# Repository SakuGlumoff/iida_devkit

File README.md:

# Iida devkit

PCB design exercise

## Hardware

Hardware design related files can be found in the `hardware` directory.
To get started with hardware development, take a look at the _README_ file therein.

The harware was designed with [KiCad EDA](https://www.kicad.org/) and manufactured with [Aisler](https://aisler.net/).

## Firmware

Firmware source files can be found in the `firmware` directory.
To get started with firmware development, take a look at the _README_ file therein.

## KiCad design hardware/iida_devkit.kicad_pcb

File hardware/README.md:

# Hardware

Hardware for Iida devkit.

## Requirements

| Tool  | Version |
|-------|---------|
| KiCad | >= 8    |
| Git   | >= 2.34 |

## How to get started

Install the required version of _KiCad_ from https://www.kicad.org/download/.
Install the required version of _Git_ from https://git-scm.com/downloads.
Download the symbol and part libraries used in this project by running `git submodule update --init --recursive`.
You can now open the project file `iida_devkit.kicad_pro` with _KiCad_.

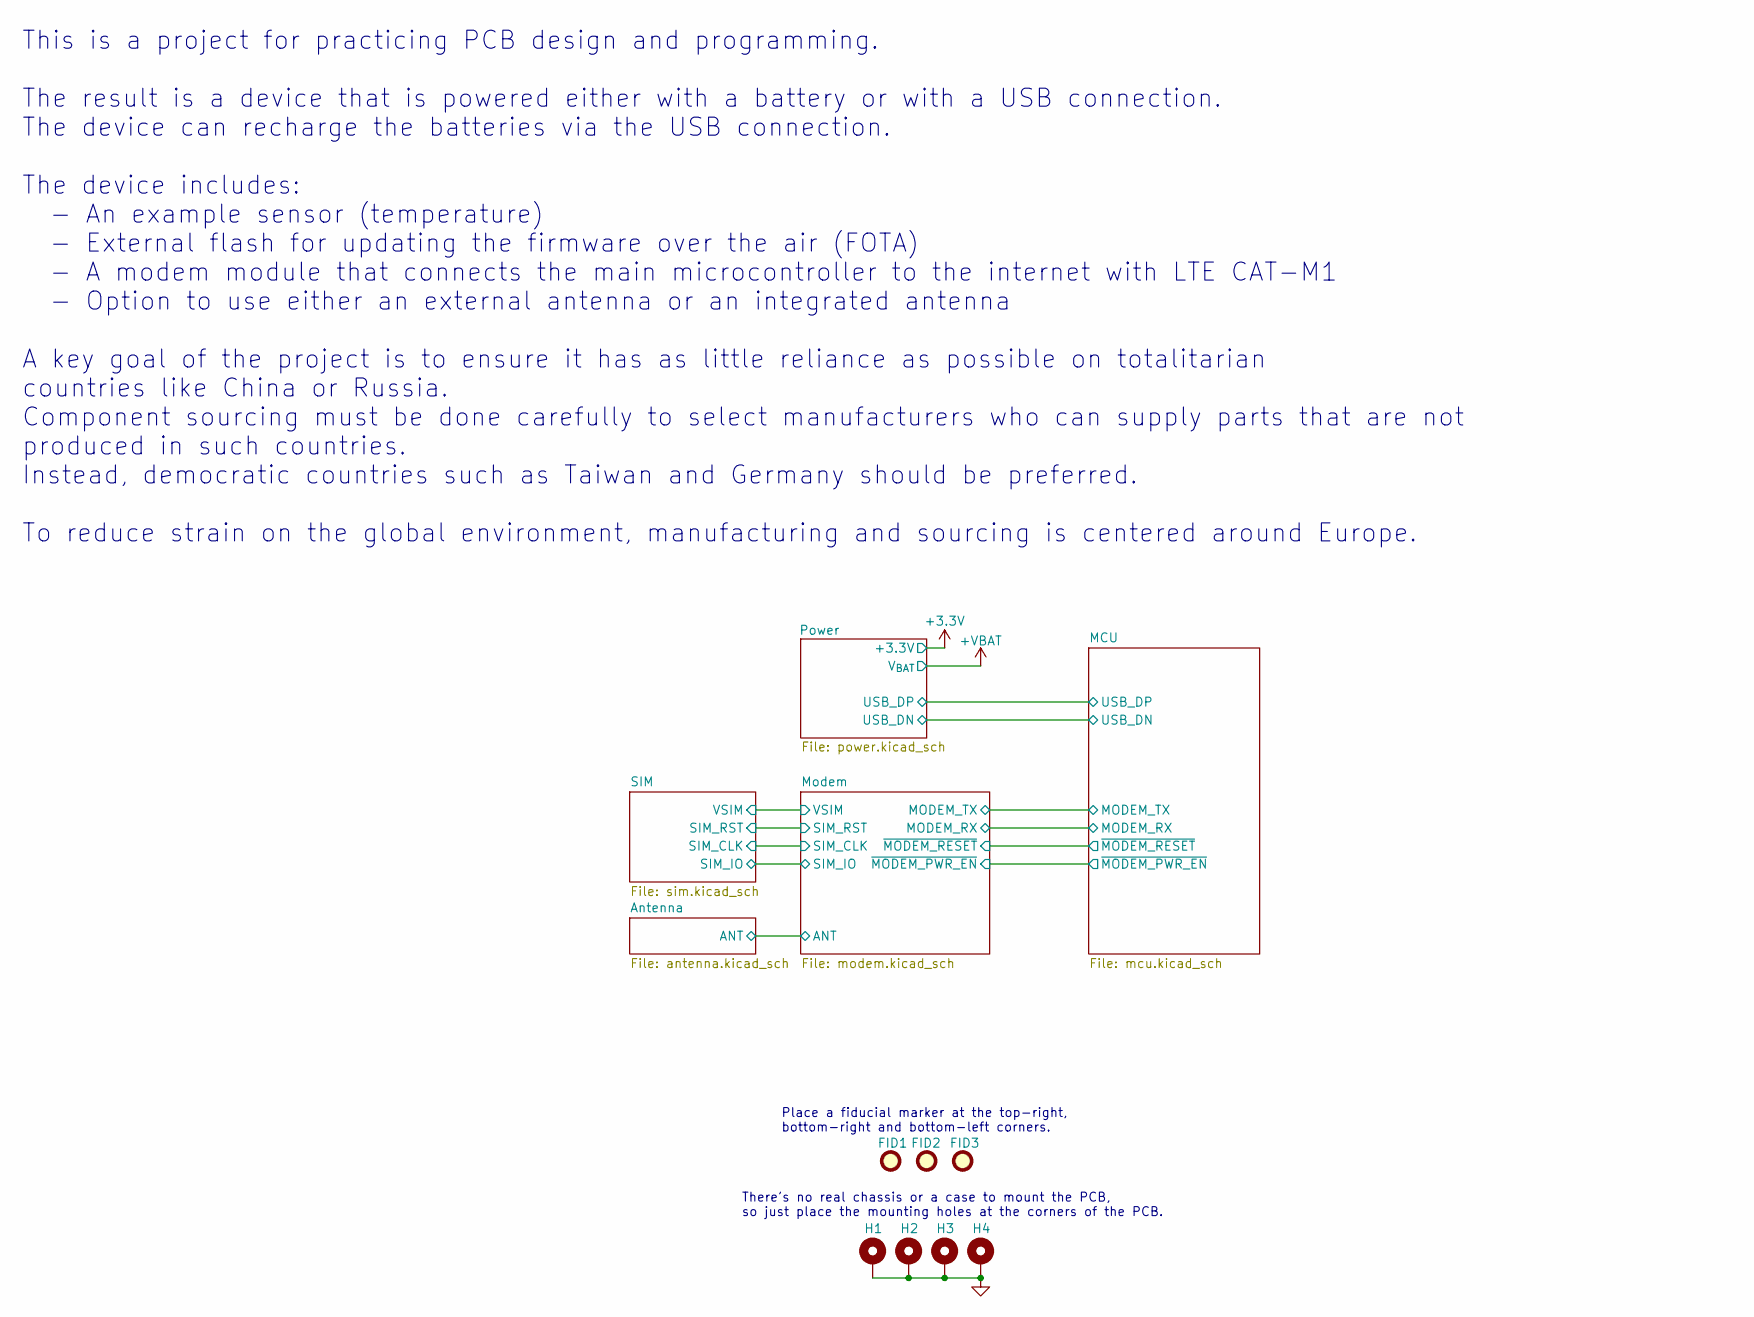
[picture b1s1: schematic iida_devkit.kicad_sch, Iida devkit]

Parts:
FID1, FID2, FID3: Fiducial; Fiducial_1mm_Mask2mm
H1, H2, H3, H4: MountingHole_Pad; MountingHole_2.2mm_M2_Pad_Via

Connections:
GND: H1.1, H2.1, H3.1, H4.1; also elsewhere on the board

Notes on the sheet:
There's no real chassis or a case to mount the PCB, so just place the mounting holes at the corners of the PCB.
Place a fiducial marker at the top-right, bottom-right and bottom-left corners.
This is a project for practicing PCB design and programming. The result is a device that is powered either with a battery or with a USB connection. The device can recharge the batteries via the USB connection. The device includes: - An example sensor (temperature) - External flash for updating the 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

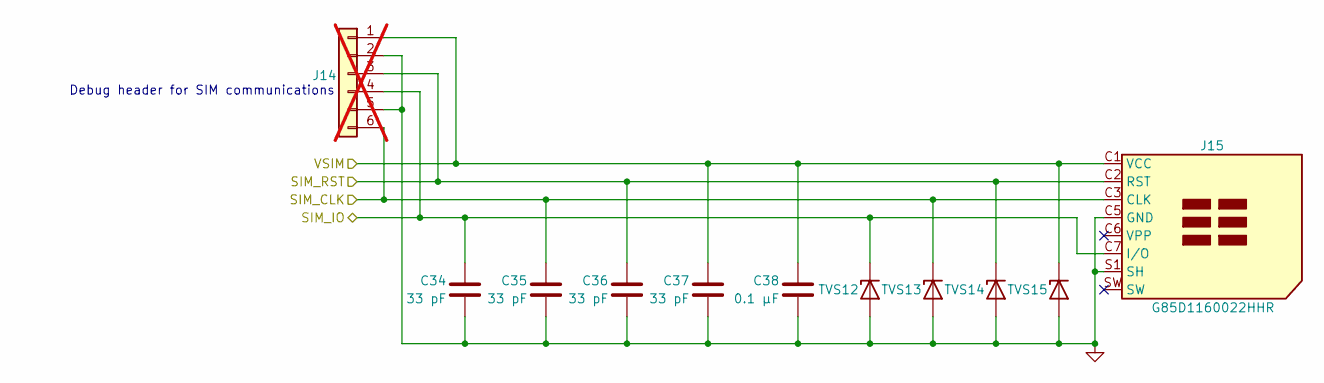
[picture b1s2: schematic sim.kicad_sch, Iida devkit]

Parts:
C34, C35, C36, C37: 33 pF; C_0603_1608Metric_Pad1.08x0.95mm_HandSolder; Manufacturer Part Number 885012006005; Digi-Key Part Number 732-7749-1-ND
C38: 0.1 µF; C_0603_1608Metric_Pad1.08x0.95mm_HandSolder; Manufacturer Part Number 885012206071; Digi-Key Part Number 732-7989-1-ND
J14: PRPC006SAAN-RC; PinHeader_1x06_P2.54mm_Vertical; Manufacturer Part Number PRPC006SAAN-RC; Digi-Key Part Number S1011EC-06-ND; not fitted
J15: G85D1160022HHR; AMPHENOL_G85D1160022HHR; Manufacturer Part Number G85D1160022HHR; Digi-Key Part Number 664-G85D1160022HHRCT-ND
TVS12, TVS13, TVS14, TVS15: CPDUC5V0USP-HF; D_0603_1608Metric_Pad1.05x0.95mm_HandSolder; Manufacturer Part Number CPDUC5V0USP-HF; Digi-Key Part Number 641-1765-1-ND

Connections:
/Modem/SIM_CLK: C35.1, J14.6, J15.C3 (CLK), TVS13.1 (K); also elsewhere on the board
/Modem/SIM_IO: C34.1, J14.4, J15.C7 (I/O), TVS12.1 (K); also elsewhere on the board
/Modem/SIM_RST: C36.1, J14.3, J15.C2 (RST), TVS14.1 (K); also elsewhere on the board
/Modem/VSIM: C37.1, C38.1, J14.1, J15.C1 (VCC), TVS15.1 (K); also elsewhere on the board
GND: C34.2, C35.2, C36.2, C37.2, C38.2, J14.2, J14.5, J15.C5 (GND), J15.S1 (SH), J15.S2 (SH), J15.S3 (SH), TVS12.2 (A), TVS13.2 (A), TVS14.2 (A), TVS15.2 (A); also elsewhere on the board

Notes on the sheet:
Debug header for SIM communications

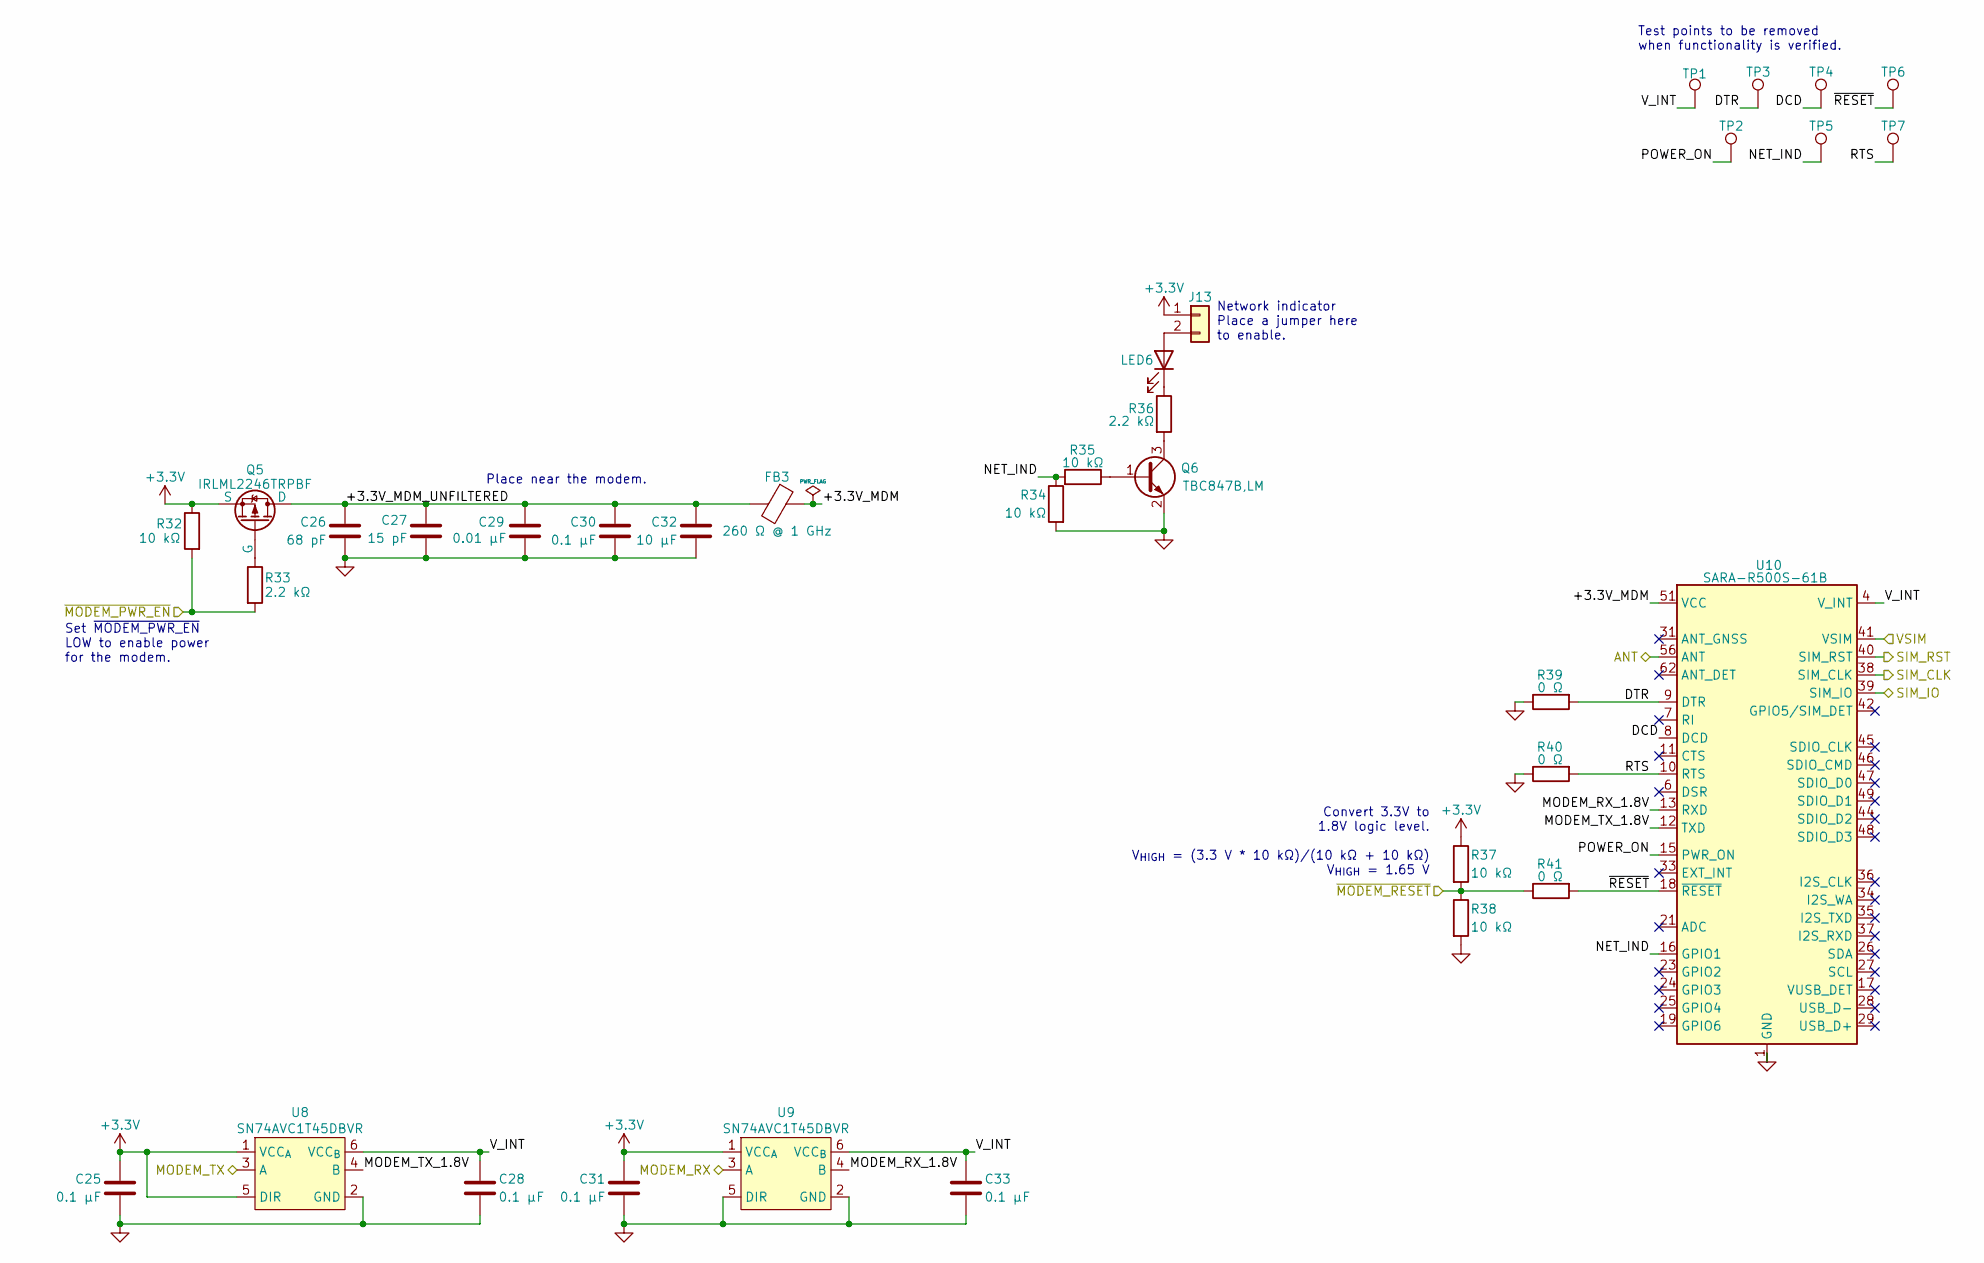
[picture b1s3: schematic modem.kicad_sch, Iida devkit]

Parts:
C25, C28, C30, C31, C33: 0.1 µF; C_0603_1608Metric_Pad1.08x0.95mm_HandSolder; Manufacturer Part Number 885012206071; Digi-Key Part Number 732-7989-1-ND
C26: 68 pF; C_0603_1608Metric_Pad1.08x0.95mm_HandSolder; Manufacturer Part Number 885012006037; Digi-Key Part Number 732-7779-1-ND
C27: 15 pF; C_0603_1608Metric_Pad1.08x0.95mm_HandSolder; Manufacturer Part Number 885012006003; Digi-Key Part Number 732-7747-1-ND
C29: 0.01 µF; C_0603_1608Metric_Pad1.08x0.95mm_HandSolder; Manufacturer Part Number 885012206089; Digi-Key Part Number 732-8007-1-ND
C32: 10 µF; C_0603_1608Metric_Pad1.08x0.95mm_HandSolder; Manufacturer Part Number 885012106006; Digi-Key Part Number 732-7903-1-ND
FB3: 260 Ω @ 1 GHz; R_0603_1608Metric_Pad0.98x0.95mm_HandSolder; Manufacturer Part Number BLM18EG221SN1D; Digi-Key Part Number 490-3992-1-ND
J13: PRPC001DAAN-RC; PinHeader_1x02_P2.54mm_Vertical; Manufacturer Part Number PRPC001DAAN-RC; Digi-Key Part Number S2011EC-01-ND
LED6: 150141YS73100; LED_PLCC_2835_Handsoldering; Manufacturer Part Number 150141YS73100; Digi-Key Part Number 732-5004-1-ND
Q5: IRLML2246TRPBF; SC-59_Handsoldering; Manufacturer Part Number IRLML2246TRPBF; Digi-Key Part Number IRLML2246TRPBFCT-ND
Q6: TBC847B,LM; SC-59_Handsoldering; Manufacturer Part Number TBC847B,LM; Digi-Key Part Number TBC847BLMCT-ND
R32, R34, R35, R37, R38: 10 kΩ; R_0603_1608Metric_Pad0.98x0.95mm_HandSolder; Manufacturer Part Number 560112116005; Digi-Key Part Number 732-560112116005CT-ND
R33, R36: 2.2 kΩ; R_0603_1608Metric_Pad0.98x0.95mm_HandSolder; Manufacturer Part Number 560112116098; Digi-Key Part Number 732-560112116098CT-ND
R39, R40, R41: 0 Ω; R_0805_2012Metric_Pad1.20x1.40mm_HandSolder; Manufacturer Part Number 560112120002; Digi-Key Part Number 732-560112120002CT-ND
TP1, TP2, TP3, TP4, TP5, TP6, TP7: TestPoint; TestPoint_Pad_D1.5mm
U8, U9: SN74AVC1T45DBVR; SOT-23-6_Handsoldering; Manufacturer Part Number SN74AVC1T45DBVR; Digi-Key Part Number 296-19094-1-ND
U10: SARA-R500S-61B; ublox_SARA_LGA-96; Manufacturer Part Number SARA-R500S-61B; Digi-Key Part Number 672-SARA-R500S-61BCT-ND

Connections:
+3.3V: C25.1, C31.1, J13.1, Q5.3 (S), R32.1, R37.1, U8.1 (VCC_{A}), U8.5 (DIR), U9.1 (VCC_{A}); also elsewhere on the board
/Antenna/ANT: U10.56 (ANT); also elsewhere on the board
/MCU/MODEM_RX: U9.3 (A); also elsewhere on the board
/MCU/MODEM_TX: U8.3 (A); also elsewhere on the board
/MCU/~MODEM_PWR_EN: R32.2, R33.2; also elsewhere on the board
/MCU/~MODEM_RESET: R37.2, R38.1, R41.1; also elsewhere on the board
/Modem/+3.3V_MDM: FB3.1, U10.51 (VCC), U10.52 (VCC), U10.53 (VCC)
/Modem/+3.3V_MDM_UNFILTERED: C26.1, C27.1, C29.1, C30.1, C32.1, FB3.2, Q5.1 (D)
/Modem/DCD: TP4.1, U10.8 (DCD)
/Modem/DTR: R39.2, TP3.1, U10.9 (DTR)
/Modem/MODEM_RX_1.8V: U9.4 (B), U10.13 (RXD)
/Modem/MODEM_TX_1.8V: U8.4 (B), U10.12 (TXD)
/Modem/NET_IND: R34.1, R35.2, TP5.1, U10.16 (GPIO1)
/Modem/POWER_ON: TP2.1, U10.15 (PWR_ON)
/Modem/RTS: R40.2, TP7.1, U10.10 (RTS)
/Modem/SIM_CLK: U10.38 (SIM_CLK); also elsewhere on the board
/Modem/SIM_IO: U10.39 (SIM_IO); also elsewhere on the board
/Modem/SIM_RST: U10.40 (SIM_RST); also elsewhere on the board
/Modem/VSIM: U10.41 (VSIM); also elsewhere on the board
/Modem/V_INT: C28.1, C33.1, TP1.1, U8.6 (VCC_{B}), U9.6 (VCC_{B}), U10.4 (V_INT)
/Modem/~RESET: R41.2, TP6.1, U10.18 (~RESET)
GND: C25.2, C26.2, C27.2, C28.2, C29.2, C30.2, C31.2, C32.2, C33.2, Q6.2 (E), R34.2, R38.2, R39.1, R40.1, U8.2 (GND), U9.2 (GND), U9.5 (DIR), U10.1 (GND), U10.3 (GND), U10.5 (GND), U10.14 (GND), U10.20 (GND), U10.22 (GND), U10.30 (GND), U10.32 (GND), U10.43 (GND), U10.50 (GND), U10.54 (GND), U10.55 (GND), U10.57 (GND), U10.58 (GND), U10.59 (GND), U10.60 (GND), U10.61 (GND), U10.63 (GND), U10.64 (GND), U10.65 (GND), U10.66 (GND), U10.67 (GND), U10.68 (GND), U10.69 (GND), U10.70 (GND), U10.71 (GND), U10.72 (GND), U10.73 (GND), U10.74 (GND), U10.75 (GND), U10.76 (GND), U10.77 (GND), U10.78 (GND), U10.79 (GND), U10.80 (GND), U10.81 (GND), U10.82 (GND), U10.83 (GND), U10.84 (GND), U10.85 (GND), U10.86 (GND), U10.87 (GND), U10.88 (GND), U10.89 (GND), U10.90 (GND), U10.91 (GND), U10.92 (GND), U10.93 (GND), U10.94 (GND), U10.95 (GND), U10.96 (GND); also elsewhere on the board
unnamed: J13.2, LED6.2 (A)
unnamed: LED6.1 (K), R36.1
unnamed: Q5.2 (G), R33.1
unnamed: Q6.1 (B), R35.1
unnamed: Q6.3 (C), R36.2

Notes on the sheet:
Convert 3.3V to 1.8V logic level. V_{HIGH} = (3.3 V * 10 kΩ)/(10 kΩ + 10 kΩ) V_{HIGH} = 1.65 V
Place near the modem.
Set ~{MODEM_PWR_EN} LOW to enable power for the modem.
Test points to be removed when functionality is verified.
Network indicator Place a jumper here to enable.

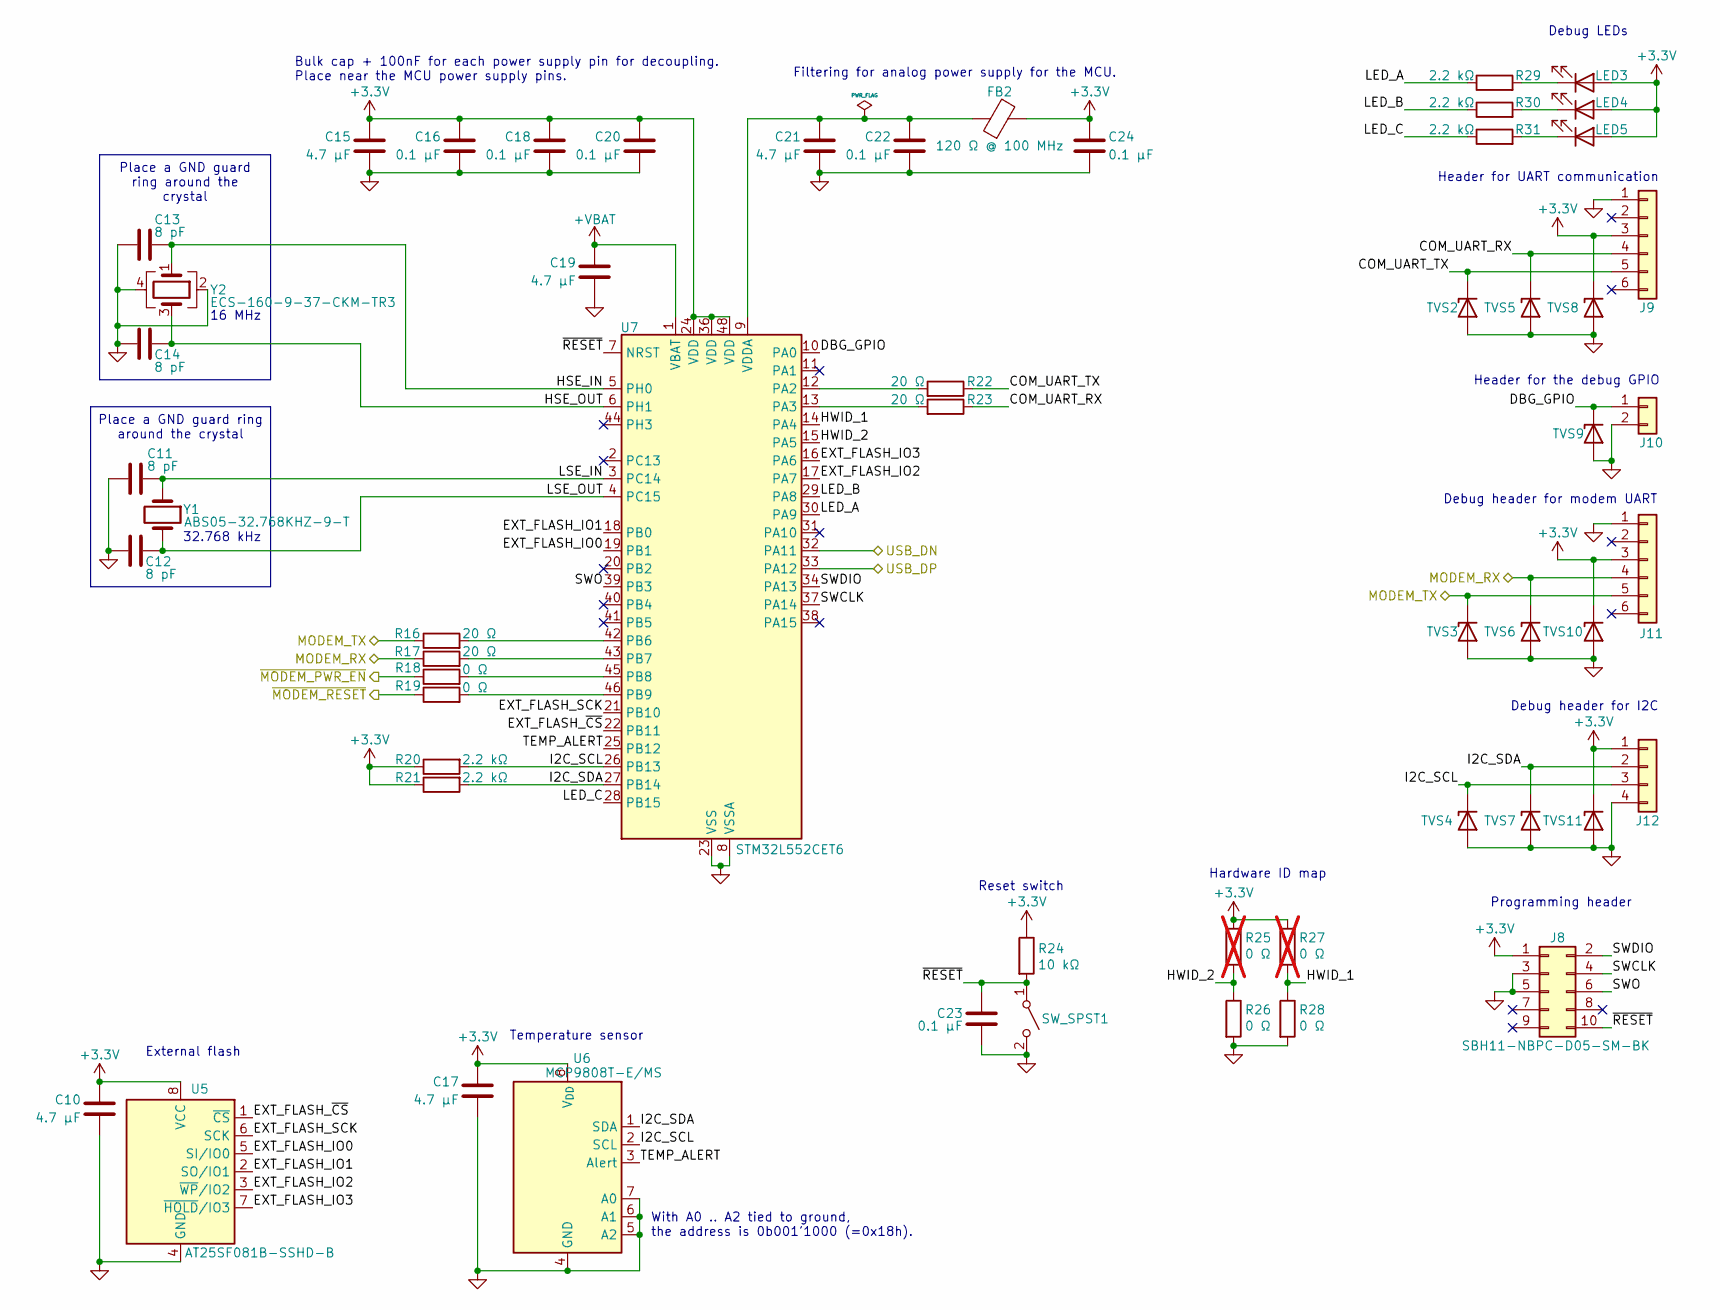
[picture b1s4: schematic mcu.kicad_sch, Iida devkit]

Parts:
C10, C15, C17, C19, C21: 4.7 µF; C_0805_2012Metric_Pad1.18x1.45mm_HandSolder; Manufacturer Part Number 885012107013; Digi-Key Part Number 732-7623-1-ND
C11, C12, C13, C14: 8 pF; C_0603_1608Metric_Pad1.08x0.95mm_HandSolder; Manufacturer Part Number 885012006093; Digi-Key Part Number 732-12050-1-ND
C16, C18, C20, C22, C23, C24: 0.1 µF; C_0603_1608Metric_Pad1.08x0.95mm_HandSolder; Manufacturer Part Number 885012206071; Digi-Key Part Number 732-7989-1-ND
FB2: 120 Ω @ 100 MHz; R_0603_1608Metric_Pad0.98x0.95mm_HandSolder; Manufacturer Part Number BLM18KG121TN1D; Digi-Key Part Number 490-5254-1-ND
J8: SBH11-NBPC-D05-SM-BK; IDC-Header_2x05_P2.54mm_Vertical_SMD; Manufacturer Part Number SBH11-NBPC-D05-SM-BK; Digi-Key Part Number S9185-ND
J9, J11: PRPC006SAAN-RC; PinHeader_1x06_P2.54mm_Vertical; Manufacturer Part Number PRPC006SAAN-RC; Digi-Key Part Number S1011EC-06-ND
J10: PRPC001DAAN-RC; PinHeader_1x02_P2.54mm_Vertical; Manufacturer Part Number PRPC001DAAN-RC; Digi-Key Part Number S2011EC-01-ND
J12: PRPC004SAAN-RC; PinHeader_1x04_P2.54mm_Vertical; Manufacturer Part Number PRPC004SAAN-RC; Digi-Key Part Number S1011EC-04-ND
LED3, LED4, LED5: 150141YS73100; LED_PLCC_2835_Handsoldering; Manufacturer Part Number 150141YS73100; Digi-Key Part Number 732-5004-1-ND
R16, R17, R22, R23: 20 Ω; R_0603_1608Metric_Pad0.98x0.95mm_HandSolder; Manufacturer Part Number 560112116125; Digi-Key Part Number 732-560112116125CT-ND
R18, R19, R26, R28: 0 Ω; R_0805_2012Metric_Pad1.20x1.40mm_HandSolder; Manufacturer Part Number 560112120002; Digi-Key Part Number 732-560112120002CT-ND
R20, R21, R29, R30, R31: 2.2 kΩ; R_0603_1608Metric_Pad0.98x0.95mm_HandSolder; Manufacturer Part Number 560112116098; Digi-Key Part Number 732-560112116098CT-ND
R24: 10 kΩ; R_0603_1608Metric_Pad0.98x0.95mm_HandSolder; Manufacturer Part Number 560112116005; Digi-Key Part Number 732-560112116005CT-ND
R25, R27: 0 Ω; R_0805_2012Metric_Pad1.20x1.40mm_HandSolder; Manufacturer Part Number 560112120002; Digi-Key Part Number 732-560112120002CT-ND; not fitted
SW_SPST1: 430182050816; SW_SPST_PTS645; Manufacturer Part Number 430182050816; Digi-Key Part Number 732-7005-1-ND
TVS2, TVS3, TVS4, TVS5, TVS6, TVS7, TVS8, TVS9, TVS10, TVS11: CPDUC5V0USP-HF; D_0603_1608Metric_Pad1.05x0.95mm_HandSolder; Manufacturer Part Number CPDUC5V0USP-HF; Digi-Key Part Number 641-1765-1-ND
U5: AT25SF081B-SSHD-B; SOIC-8_3.9x4.9mm_P1.27mm; Manufacturer Part Number AT25SF081B-SSHD-B; Digi-Key Part Number 1265-AT25SF081B-SSHD-B-ND
U6: MCP9808T-E/MS; MSOP-8_3x3mm_P0.65mm; Manufacturer Part Number MCP9808T-E/MS; Digi-Key Part Number MCP9808T-E/MSCT-ND
U7: STM32L552CET6; LQFP-48_7x7mm_P0.5mm; Manufacturer Part Number STM32L552CET6; Digi-Key Part Number 497-STM32L552CET6-ND
Y1: ABS05-32.768KHZ-9-T; Crystal_SMD_MicroCrystal_CM9V-T1A-2Pin_1.6x1.0mm_HandSolder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; Manufacturer Part Number ABS05-32.768KHZ-9-T; Digi-Key Part Number 535-ABS05-32.768KHZ-9-TCT-ND
Y2: ECS-160-9-37-CKM-TR3; Crystal_SMD_3225-4Pin_3.2x2.5mm_HandSoldering; Manufacturer Part Number ECS-160-9-33B-CKM-TR3; Digi-Key Part Number 50-ECS-160-9-33B-CKM-TR3CT-ND

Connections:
+3.3V: C10.1, C15.1, C16.1, C17.1, C18.1, C20.1, C24.1, FB2.2, J8.1, J9.3, J11.3, J12.1, LED3.2 (A), LED4.2 (A), LED5.2 (A), R20.1, R21.1, R24.1, R25.1, R27.1, TVS8.1 (K), TVS10.1 (K), TVS11.1 (K), U5.8 (VCC), U6.8 (V_{DD}), U7.24 (VDD), U7.36 (VDD), U7.48 (VDD); also elsewhere on the board
+VBAT: C19.1, U7.1 (VBAT); also elsewhere on the board
/MCU/COM_UART_RX: J9.4, R23.1, TVS5.1 (K)
/MCU/COM_UART_TX: J9.5, R22.1, TVS2.1 (K)
/MCU/DBG_GPIO: J10.1, TVS9.1 (K), U7.10 (PA0)
/MCU/EXT_FLASH_IO0: U5.5 (SI/IO0), U7.19 (PB1)
/MCU/EXT_FLASH_IO1: U5.2 (SO/IO1), U7.18 (PB0)
/MCU/EXT_FLASH_IO2: U5.3 (~WP/IO2), U7.17 (PA7)
/MCU/EXT_FLASH_IO3: U5.7 (~HOLD/IO3), U7.16 (PA6)
/MCU/EXT_FLASH_SCK: U5.6 (SCK), U7.21 (PB10)
/MCU/EXT_FLASH_~CS: U5.1 (~CS), U7.22 (PB11)
/MCU/HSE_IN: C13.1, U7.5 (PH0), Y2.1
/MCU/HSE_OUT: C14.1, U7.6 (PH1), Y2.3
/MCU/HWID_1: R27.2, R28.1, U7.14 (PA4)
/MCU/HWID_2: R25.2, R26.1, U7.15 (PA5)
/MCU/I2C_SCL: J12.3, R20.2, TVS4.1 (K), U6.2 (SCL), U7.26 (PB13)
/MCU/I2C_SDA: J12.2, R21.2, TVS7.1 (K), U6.1 (SDA), U7.27 (PB14)
/MCU/LED_A: R29.1, U7.30 (PA9)
/MCU/LED_B: R30.1, U7.29 (PA8)
/MCU/LED_C: R31.1, U7.28 (PB15)
/MCU/LSE_IN: C11.1, U7.3 (PC14), Y1.1
/MCU/LSE_OUT: C12.1, U7.4 (PC15), Y1.2
/MCU/MODEM_RX: J11.4, R17.1, TVS6.1 (K); also elsewhere on the board
/MCU/MODEM_TX: J11.5, R16.1, TVS3.1 (K); also elsewhere on the board
/MCU/SWCLK: J8.4, U7.37 (PA14)
/MCU/SWDIO: J8.2, U7.34 (PA13)
/MCU/SWO: J8.6, U7.39 (PB3)
/MCU/TEMP_ALERT: U6.3 (Alert), U7.25 (PB12)
/MCU/USB_DN: U7.32 (PA11); also elsewhere on the board
/MCU/USB_DP: U7.33 (PA12); also elsewhere on the board
/MCU/~MODEM_PWR_EN: R18.1; also elsewhere on the board
/MCU/~MODEM_RESET: R19.1; also elsewhere on the board
/MCU/~RESET: C23.2, J8.10, R24.2, SW_SPST1.1 (A), U7.7 (NRST)
GND: C10.2, C11.2, C12.2, C13.2, C14.2, C15.2, C16.2, C17.2, C18.2, C19.2, C20.2, C21.2, C22.2, C23.1, C24.2, J8.3, J8.5, J9.1, J10.2, J11.1, J12.4, R26.2, R28.2, SW_SPST1.2 (B), TVS2.2 (A), TVS3.2 (A), TVS4.2 (A), TVS5.2 (A), TVS6.2 (A), TVS7.2 (A), TVS8.2 (A), TVS9.2 (A), TVS10.2 (A), TVS11.2 (A), U5.4 (GND), U6.4 (GND), U6.5 (A2), U6.6 (A1), U6.7 (A0), U7.8 (VSSA), U7.23 (VSS), U7.35 (VSS), U7.47 (VSS), Y2.2, Y2.4; also elsewhere on the board
unnamed: LED3.1 (K), R29.2
unnamed: LED4.1 (K), R30.2
unnamed: LED5.1 (K), R31.2
unnamed: R22.2, U7.12 (PA2)
unnamed: R23.2, U7.13 (PA3)
unnamed: R16.2, U7.42 (PB6)
unnamed: R17.2, U7.43 (PB7)
unnamed: R18.2, U7.45 (PB8)
unnamed: R19.2, U7.46 (PB9)
unnamed: C21.1, C22.1, FB2.1, U7.9 (VDDA)

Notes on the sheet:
Place a GND guard ring around the crystal
Programming header
Reset switch
External flash
Header for the debug GPIO
Temperature sensor
Debug header for modem UART
Hardware ID map
Filtering for analog power supply for the MCU.
Debug LEDs
Debug header for I2C
Header for UART communication
16 MHz
32.768 kHz
With A0 .. A2 tied to ground, the address is 0b001'1000 (=0x18h).
Bulk cap + 100nF for each power supply pin for decoupling. Place near the MCU power supply pins.

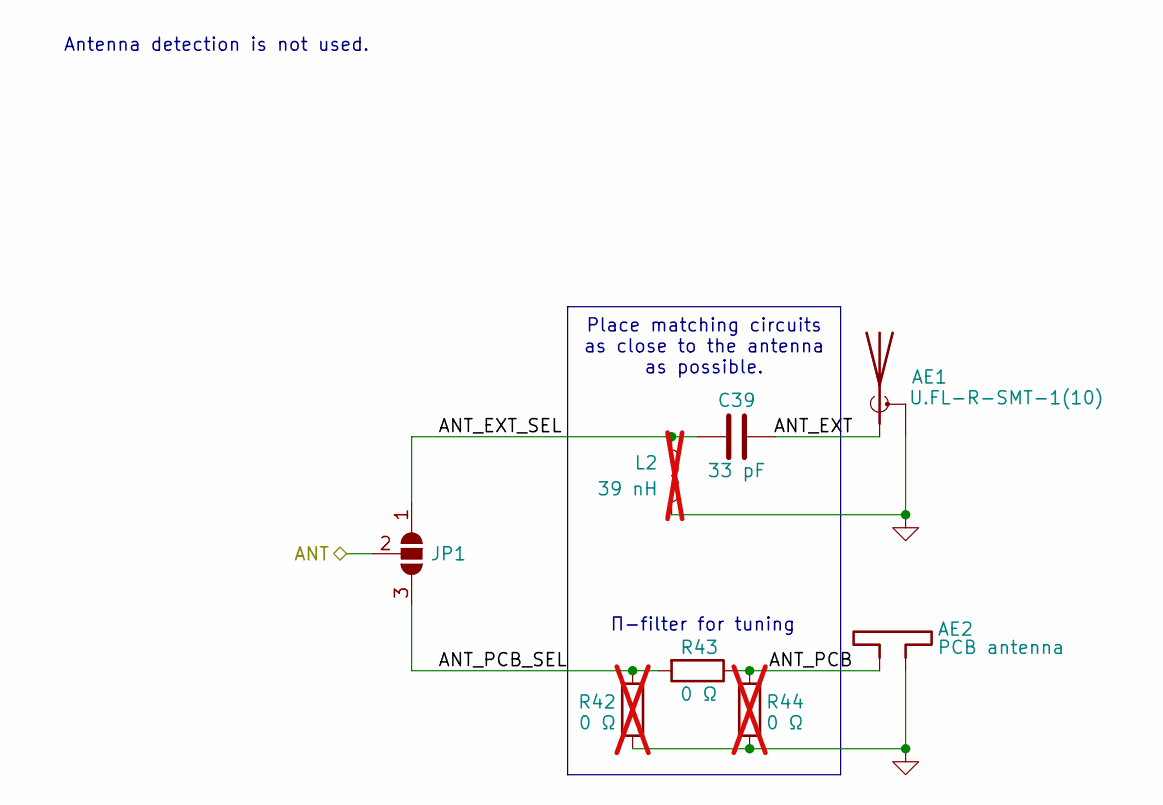
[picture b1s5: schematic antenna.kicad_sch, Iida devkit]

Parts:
AE1: U.FL-R-SMT-1(10); U.FL_Hirose_U.FL-R-SMT-1_Vertical; Manufacturer Part Number U.FL-R-SMT-1(10); Digi-Key Part Number H11891CT-ND
AE2: PCB antenna; 800MHz_antenna
C39: 33 pF; C_0603_1608Metric_Pad1.08x0.95mm_HandSolder; Manufacturer Part Number 885012006005; Digi-Key Part Number 732-7749-1-ND
JP1: SolderJumper_3_Open; 0Ohm_choice_90_degree_0402
L2: 39 nH; L_0603_1608Metric_Pad1.05x0.95mm_HandSolder; Manufacturer Part Number LQG15HS39NJ02D; Digi-Key Part Number 490-2630-1-ND; not fitted
R42, R44: 0 Ω; R_0805_2012Metric_Pad1.20x1.40mm_HandSolder; Manufacturer Part Number 560112120002; Digi-Key Part Number 732-560112120002CT-ND; not fitted
R43: 0 Ω; R_0805_2012Metric_Pad1.20x1.40mm_HandSolder; Manufacturer Part Number 560112120002; Digi-Key Part Number 732-560112120002CT-ND

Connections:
/Antenna/ANT: JP1.2 (C); also elsewhere on the board
/Antenna/ANT_EXT: AE1.1 (A), C39.1
/Antenna/ANT_EXT_SEL: C39.2, JP1.1 (A), L2.1
/Antenna/ANT_PCB: AE2.1, R43.1, R44.2
/Antenna/ANT_PCB_SEL: JP1.3 (B), R42.2, R43.2
GND: AE1.2 (Shield), AE2.2, L2.2, R42.1, R44.1; also elsewhere on the board

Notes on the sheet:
Place matching circuits as close to the antenna as possible.
Antenna detection is not used.
Π-filter for tuning
